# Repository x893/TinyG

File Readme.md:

Software from https://github.com/synthetos/TinyG

xboot-BT : change for Bluetooth module

xboot-loader : utility to upload (MS Visual Studio 2013) upload program with parameters -b 115200 -P COM14 -U flash:w:tinyg.hex

hardware : design files for http://akb77.com/g/cnc/tinyg-controller-for-cnc/

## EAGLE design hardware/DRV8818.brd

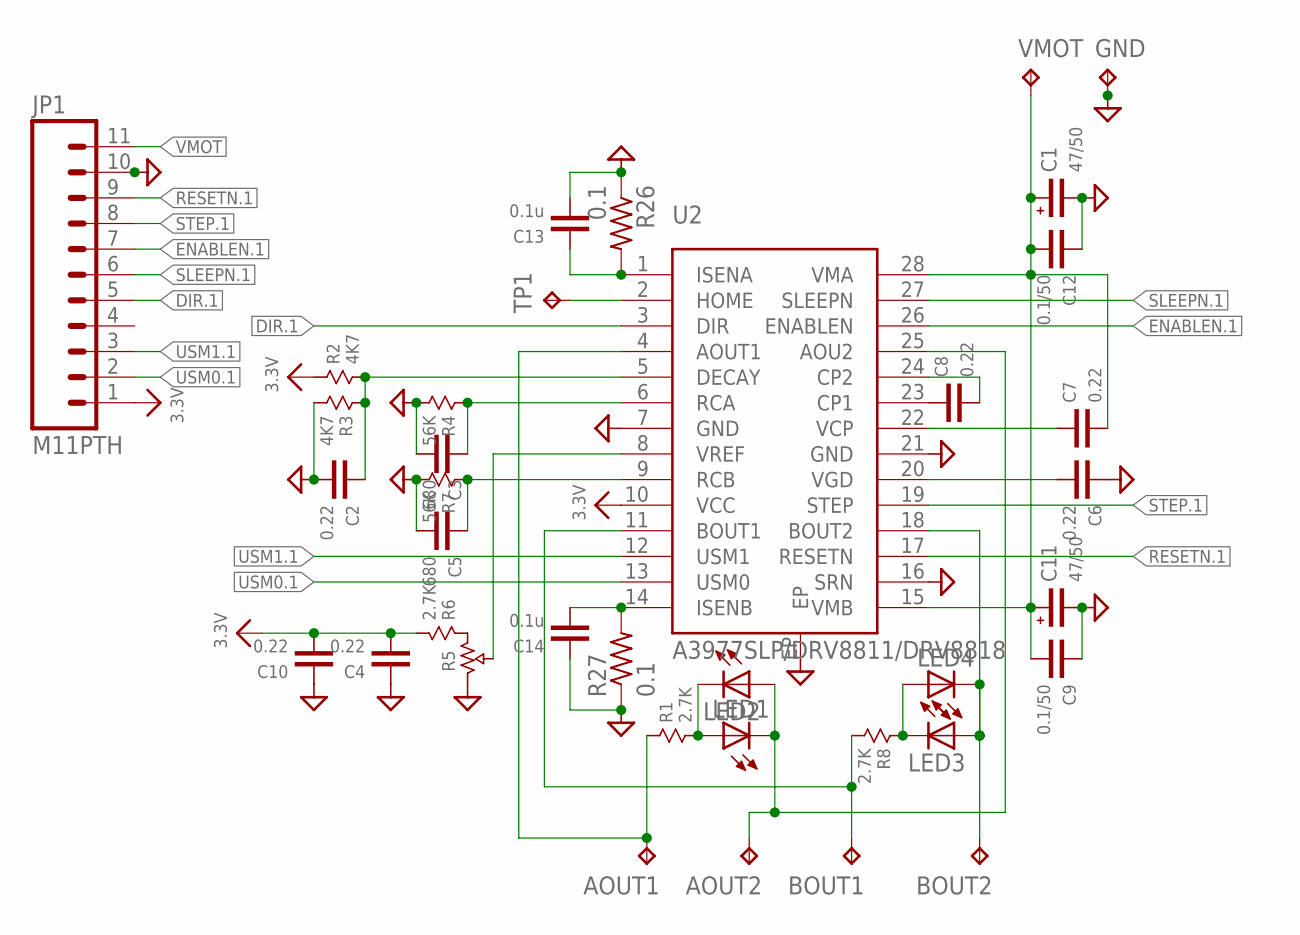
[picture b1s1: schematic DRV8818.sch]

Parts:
AOUT1, AOUT2: TPTP20R; TP20R
BOUT1, BOUT2: TPTP20R; TP20R
C1, C11: 47/50; CT7343
C2, C4, C6, C7, C8, C10: 0.22; 0603
C3, C5: 680; 0603
C9, C12: 0.1/50; 0603
C13, C14: 0.1u; 0603
GND: TPTP20R; TP20R
JP1: M11PTH; 1X11
LED1, LED2, LED3, LED4: LEDCHIP-LED0603; CHIP-LED0603
R1, R6, R8: 2.7K; 0603
R2, R3: 4K7; 0603
R4, R7: 56K; 0603
R5: PVZ3A
R26, R27: 0.1; R2512
TP1: TPTP08R; TP08R
U2: A3977SLP/DRV8811/DRV8818; SSOP28EP
VMOT: TPTP20R; TP20R

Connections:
3.3V: C4.1, C10.1, JP1.1, R2.1, R6.2, U2.10 (VCC)
AOUT1: AOUT1.TP, R1.1, U2.4 (AOUT1)
AOUT2: AOUT2.TP, LED1.C, LED2.A, U2.25 (AOU2)
BOUT1: BOUT1.TP, R8.2, U2.11 (BOUT1)
BOUT2: BOUT2.TP, LED3.A, LED4.C, U2.18 (BOUT2)
DIR.1: JP1.5, U2.3 (DIR)
ENABLEN.1: JP1.7, U2.26 (ENABLEN)
GND: C1.-, C2.1, C3.1, C4.2, C5.1, C6.2, C9.2, C10.2, C11.-, C12.2, C13.1, C14.2, GND.TP, JP1.10, R3.2, R4.2, R5.1, R7.2, R26.1, R27.1, U2.7 (GND), U2.16 (SRN), U2.21 (GND), U2.EP
unnamed: C14.1, R27.2, U2.14 (ISENB)
unnamed: LED3.C, LED4.A, R8.1
unnamed: LED1.A, LED2.C, R1.2
unnamed: C2.2, R2.2, R3.1, U2.5 (DECAY)
unnamed: C3.2, R4.1, U2.6 (RCA)
unnamed: R5.3, R6.1
unnamed: R5.2, U2.8 (VREF)
unnamed: C5.2, R7.1, U2.9 (RCB)
unnamed: C13.2, R26.2, U2.1 (ISENA)
unnamed: TP1.TP, U2.2 (HOME)
unnamed: C7.2, U2.22 (VCP)
unnamed: C6.1, U2.20 (VGD)
unnamed: C8.2, U2.23 (CP1)
unnamed: C8.1, U2.24 (CP2)
RESETN.1: JP1.9, U2.17 (RESETN)
SLEEPN.1: JP1.6, U2.27 (SLEEPN)
STEP.1: JP1.8, U2.19 (STEP)
USM0.1: JP1.2, U2.13 (USM0)
USM1.1: JP1.3, U2.12 (USM1)
VMOT: C1.+, C7.1, C9.1, C11.+, C12.1, JP1.11, U2.15 (VMB), U2.28 (VMA), VMOT.TP

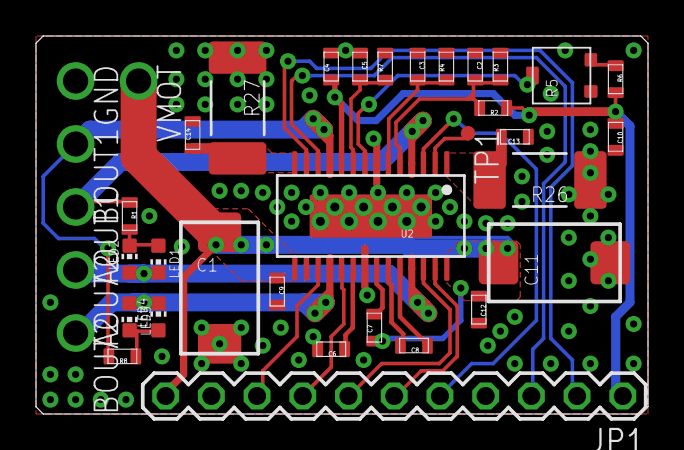
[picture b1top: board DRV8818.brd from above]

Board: 2 copper layers, 34.0 x 21.0 mm, 37 parts (0 on the bottom side), 28 nets.

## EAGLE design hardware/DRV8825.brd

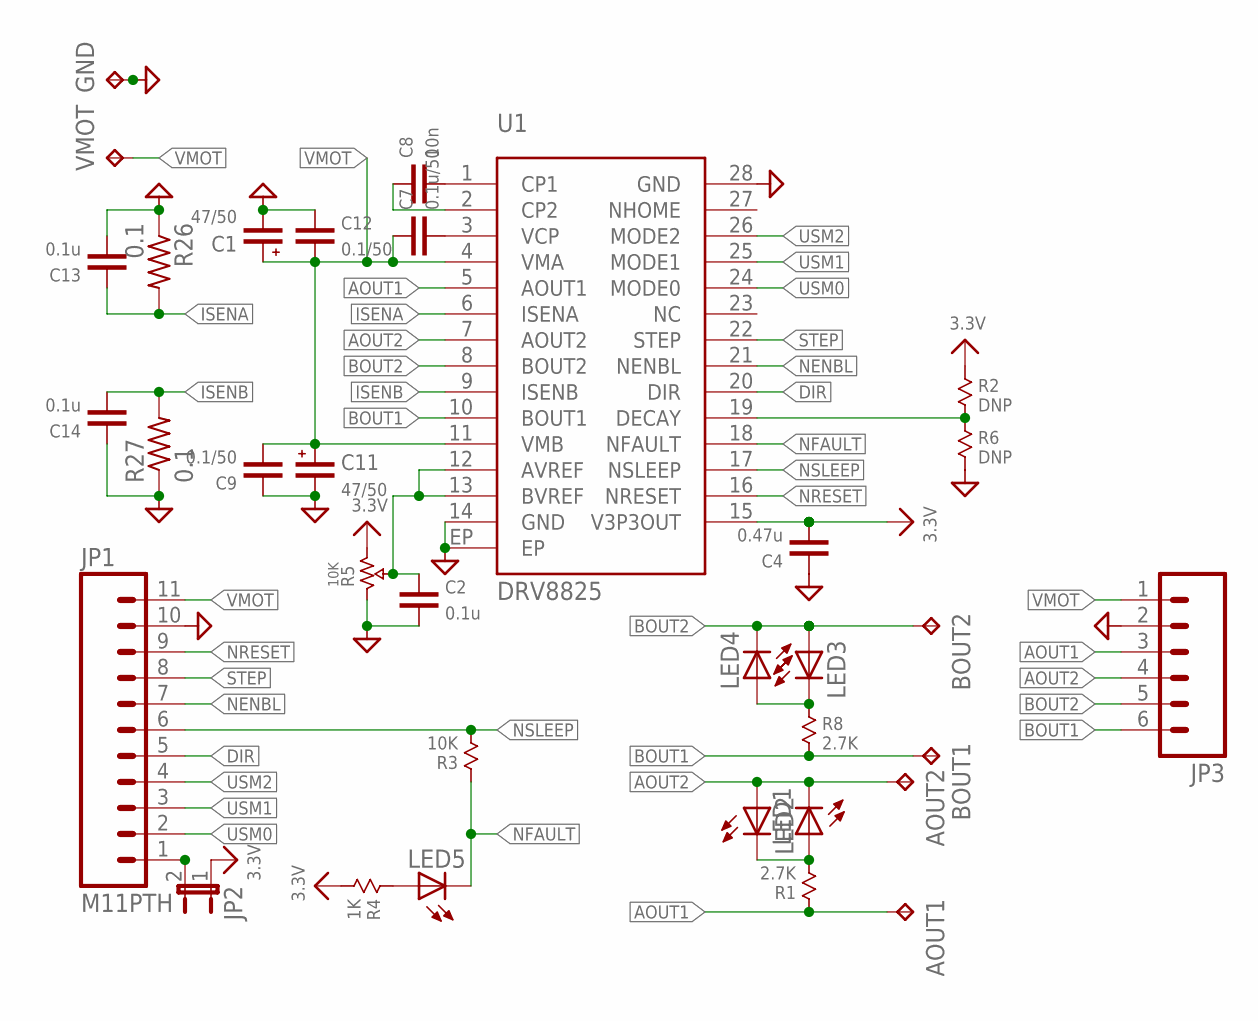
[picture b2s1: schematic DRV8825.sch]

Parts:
AOUT1, AOUT2: TPTP18R; TP18R
BOUT1, BOUT2: TPTP18R; TP18R
C1, C11: 47/50; CT7343
C2, C13, C14: 0.1u; 0603
C4: 0.47u; 0603
C7: 0.1u/50; 0603
C8: 10n; 0603
C9, C12: 0.1/50; 0603
GND: TPTP18R; TP18R
JP1: M11PTH; 1X11
JP2: JUMPER-2SMD-NO; SJ_2S-NO
JP3: M06SIP; 1X06
LED1, LED2, LED3, LED4, LED5: LEDCHIP-LED0603; CHIP-LED0603
R1, R8: 2.7K; 0603
R2, R6: DNP; 0603
R3: 10K; 0603
R4: 1K; 0603
R5: 10K; PVZ3A
R26, R27: 0.1; R2512
U1: DRV8825; SSOP28EP
VMOT: TPTP18R; TP18R

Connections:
3.3V: C4.1, JP2.1, R2.1, R4.2, R5.3, U1.15 (V3P3OUT)
AOUT1: AOUT1.TP, JP3.3, R1.1, U1.5 (AOUT1)
AOUT2: AOUT2.TP, JP3.4, LED1.C, LED2.A, U1.7 (AOUT2)
BOUT1: BOUT1.TP, JP3.6, R8.2, U1.10 (BOUT1)
BOUT2: BOUT2.TP, JP3.5, LED3.A, LED4.C, U1.8 (BOUT2)
DIR: JP1.5, U1.20 (DIR)
GND: C1.-, C2.1, C4.2, C9.2, C11.-, C12.2, C13.1, C14.2, GND.TP, JP1.10, JP3.2, R5.1, R6.2, R26.1, R27.1, U1.14 (GND), U1.28 (GND), U1.EP
ISENA: C13.2, R26.2, U1.6 (ISENA)
ISENB: C14.1, R27.2, U1.9 (ISENB)
unnamed: C8.1, U1.1 (CP1)
unnamed: LED3.C, LED4.A, R8.1
unnamed: LED1.A, LED2.C, R1.2
unnamed: C8.2, U1.2 (CP2)
unnamed: LED5.A, R4.1
unnamed: C7.1, U1.3 (VCP)
unnamed: C2.2, R5.2, U1.12 (AVREF), U1.13 (BVREF)
unnamed: R2.2, R6.1, U1.19 (DECAY)
unnamed: JP1.1, JP2.2
NENBL: JP1.7, U1.21 (NENBL)
NFAULT: LED5.C, R3.1, U1.18 (NFAULT)
NRESET: JP1.9, U1.16 (NRESET)
NSLEEP: JP1.6, R3.2, U1.17 (NSLEEP)
STEP: JP1.8, U1.22 (STEP)
USM0: JP1.2, U1.24 (MODE0)
USM1: JP1.3, U1.25 (MODE1)
USM2: JP1.4, U1.26 (MODE2)
VMOT: C1.+, C7.2, C9.1, C11.+, C12.1, JP1.11, JP3.1, U1.4 (VMA), U1.11 (VMB), VMOT.TP

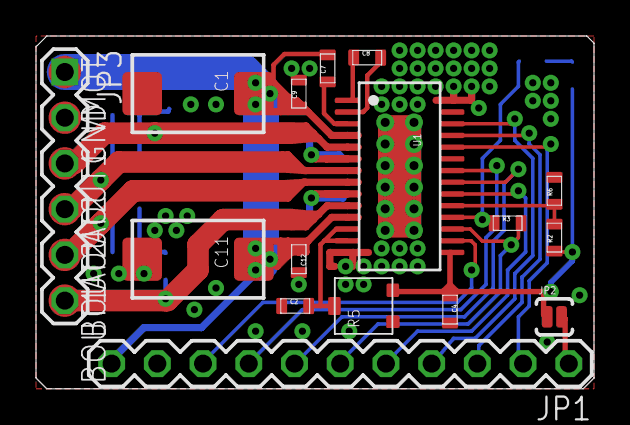
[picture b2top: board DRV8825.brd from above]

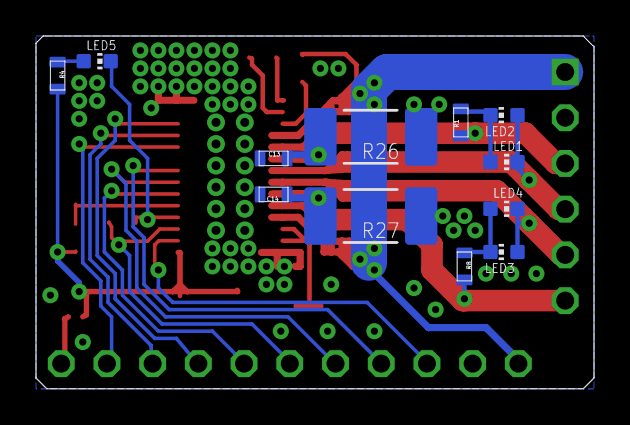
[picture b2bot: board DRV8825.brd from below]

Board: 2 copper layers, 31.0 x 19.6 mm, 34 parts (12 on the bottom side), 27 nets.

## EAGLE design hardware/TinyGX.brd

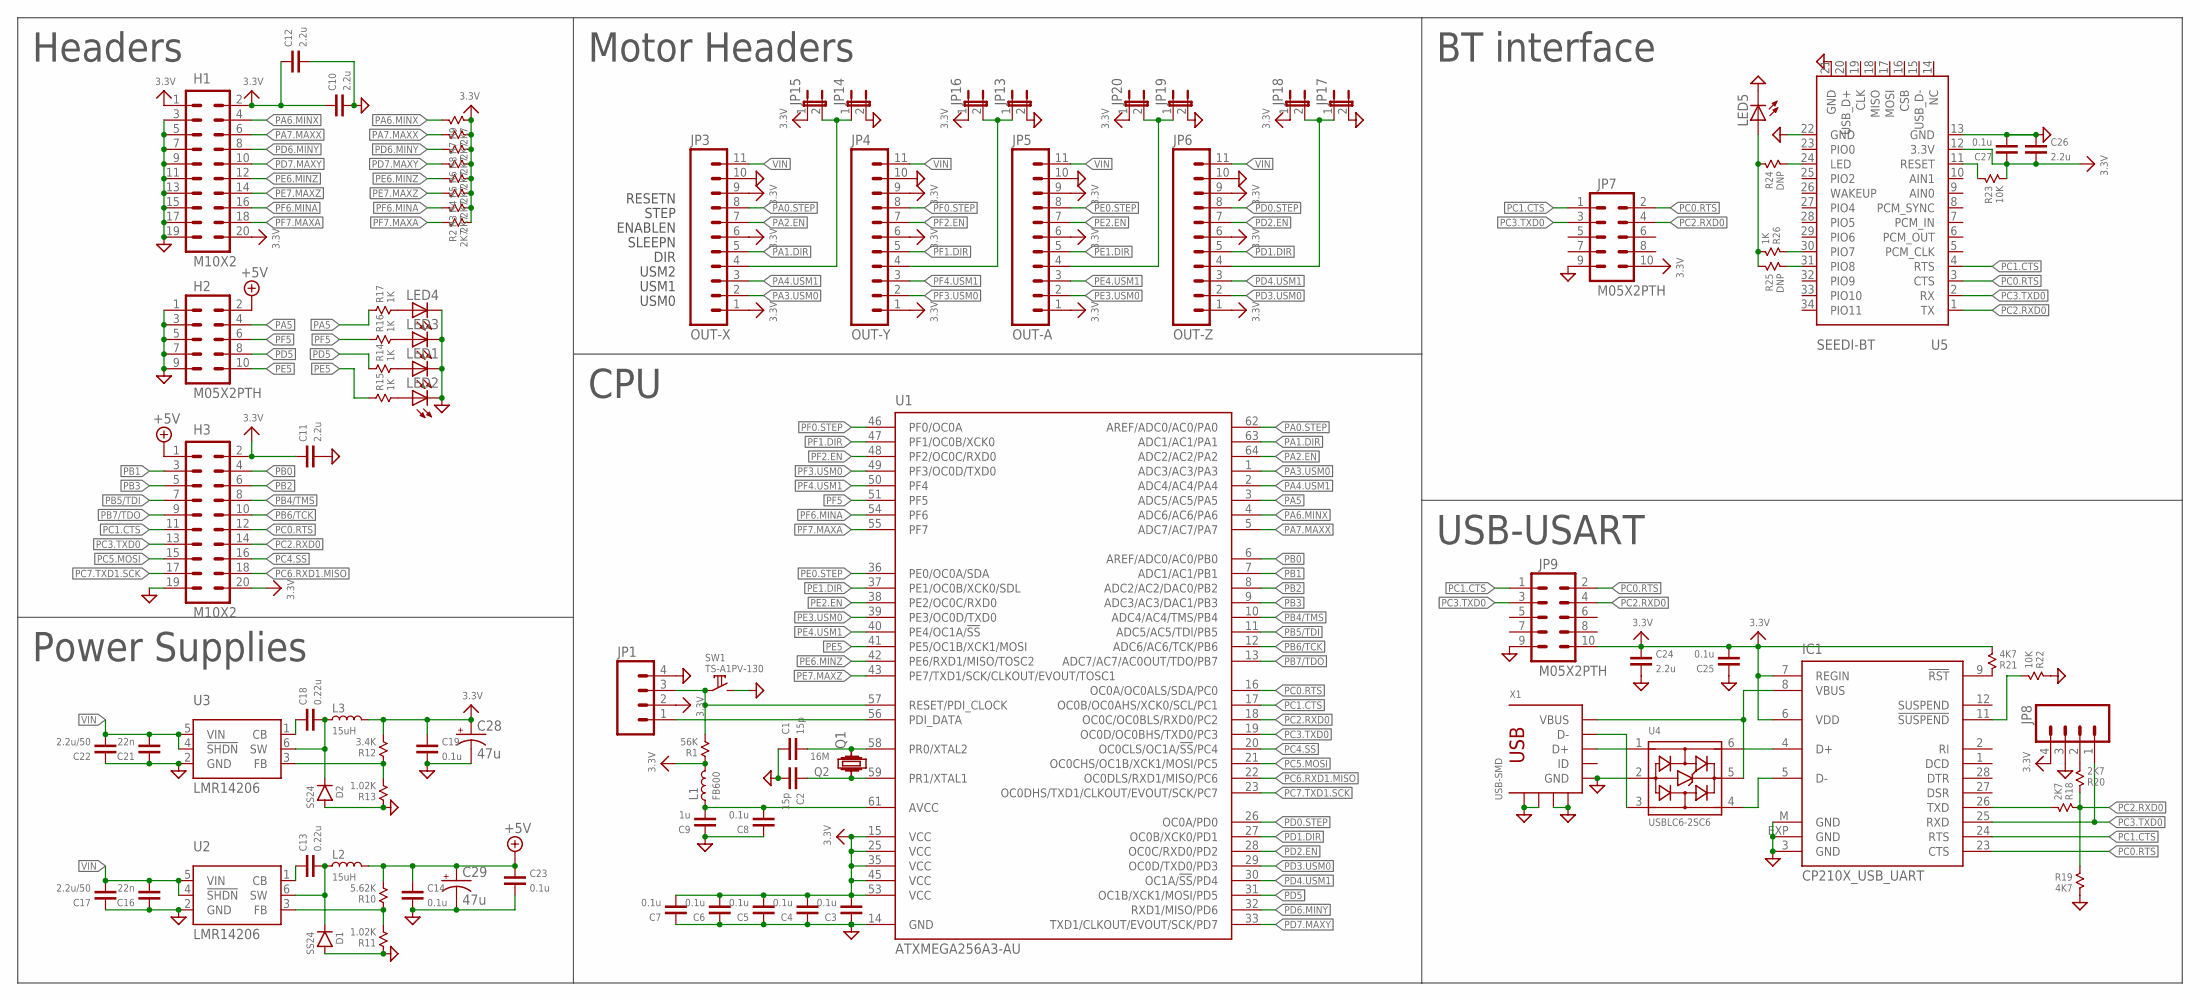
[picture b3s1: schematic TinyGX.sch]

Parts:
C1, C2: 15p; 0603
C3, C4, C5, C6, C7, C8, C14, C19, C23, C25, C27: 0.1u; 0603
C9: 1u; 0603
C10, C11, C12, C24, C26: 2.2u; 0603
C13, C18: 0.22u; 0603
C16, C21: 22n; 0603
C17, C22: 2.2u/50; 1206
C28, C29: 47u; CT3216
D1, D2: SS24; SMA
H1, H3: M10X2; 2X10
H2: M05X2PTH; AVR_ICSP
IC1: CP210X_USB_UART; MLP28
JP1, JP8: M04PTH; 1X04
JP3: OUT-X; 1X11
JP4: OUT-Y; 1X11
JP5: OUT-A; 1X11
JP6: OUT-Z; 1X11
JP7, JP9: M05X2PTH; AVR_ICSP
JP13, JP14, JP15, JP16, JP17, JP18, JP19, JP20: JUMPER-2SMD-NO; SJ_2S-NO
L1: FB600; 0603
L2, L3: 15uH; CDRH73
LED1, LED2, LED3, LED4, LED5: LEDCHIP-LED0603; CHIP-LED0603
Q1: CRYSTALHC49US; HC49US
Q2: 16M; KX-KT
R1: 56K; 0603
R2, R3, R4, R5, R6, R7, R8, R9, R18, R20: 2K7; 0603
R10: 5.62K; 0603
R11, R13: 1.02K; 0603
R12: 3.4K; 0603
R14, R15, R16, R17, R26: 1K; 0603
R19, R21: 4K7; 0603
R22, R23: 10K; 0603
R24, R25: DNP; 0603
SW1: TS-A1PV-130
U1: ATXMEGA256A3-AU; TQFP64-14X14
U2, U3: LMR14206; SOT23-6
U4: USBLC6-2SC6; SOT23-6
U5: SEEDI-BT
X1: USB-SMD; USB-MINIB

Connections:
3.3V: C3.1, C4.1, C5.1, C6.1, C7.1, C10.2, C11.2, C12.2, C19.2, C24.2, C25.1, C26.1, C27.2, C28.+, H1.1, H1.2, H1.20, H3.2, H3.20, IC1.6 (VDD), IC1.7 (REGIN), JP1.2, JP3.1, JP3.6, JP3.9, JP4.1, JP4.6, JP4.9, JP5.1, JP5.6, JP5.9, JP6.1, JP6.6, JP6.9, JP7.10, JP8.4, JP9.10, JP15.1, JP16.1, JP18.1, JP20.1, L1.2, L3.P$2 (2), R1.1, R2.2, R3.2, R4.2, R5.2, R6.2, R7.2, R8.2, R9.2, R12.2, R21.2, R23.2, U1.15 (VCC), U1.25 (VCC), U1.35 (VCC), U1.45 (VCC), U1.53 (VCC), U5.12 (3.3V)
+5V: C14.2, C23.2, C29.+, H2.2, H3.1, L2.P$2 (2), R10.2
GND: C1.2, C2.1, C3.2, C4.2, C5.2, C6.2, C7.2, C8.2, C9.2, C10.1, C11.1, C12.1, C14.1, C16.2, C17.2, C19.1, C21.2, C22.2, C23.1, C24.1, C25.2, C26.2, C27.1, C28.-, C29.-, D1.P$2 (A), D2.P$2 (A), H1.3, H1.5, H1.7, H1.9, H1.11, H1.13, H1.15, H1.17, H1.19, H2.1, H2.3, H2.5, H2.7, H2.9, H3.19, IC1.3 (GND), IC1.EXP (GND), IC1.M (GND), JP1.4, JP3.10, JP4.10, JP5.10, JP6.10, JP7.9, JP8.3, JP9.9, JP13.2, JP14.2, JP17.2, JP19.2, LED1.C, LED2.C, LED3.C, LED4.C, LED5.C, R11.1, R13.1, R19.2, R22.1, SW1.2, U1.14 (GND), U1.24 (GND), U1.34 (GND), U1.44 (GND), U1.52 (GND), U1.60 (GND), U2.2 (GND), U3.2 (GND), U4.2 (GND), U5.13 (GND), U5.21 (GND), U5.22 (GND), X1.GND, X1.GND@1 (GND), X1.GND@2 (GND), X1.GND@3 (GND), X1.GND@4 (GND)
unnamed: C1.1, Q1.2, Q2.2, U1.58 (PR0/XTAL2)
unnamed: C2.2, Q1.1, Q2.1, U1.59 (PR1/XTAL1)
unnamed: R10.1, R11.2, U2.3 (FB)
unnamed: LED1.A, R14.2
unnamed: C13.1, D1.P$1 (C), L2.P$1 (1), U2.6 (SW)
unnamed: R12.1, R13.2, U3.3 (FB)
unnamed: C13.2, U2.1 (CB)
unnamed: C8.1, C9.1, L1.1, U1.61 (AVCC)
unnamed: C18.1, D2.P$1 (C), L3.P$1 (1), U3.6 (SW)
unnamed: C18.2, U3.1 (CB)
unnamed: LED2.A, R15.2
unnamed: LED3.A, R16.2
unnamed: LED4.A, R17.2
unnamed: IC1.5 (D-), U4.4 (IO2)
unnamed: IC1.4 (D+), U4.6 (IO1)
unnamed: IC1.8 (VBUS), U4.5 (VBUS), X1.VBUS
unnamed: JP8.2, R20.2
unnamed: IC1.26 (TXD), R18.2
unnamed: IC1.9 (!RST), R21.1
unnamed: U4.3 (IO2), X1.D-
unnamed: U4.1 (IO1), X1.D+
unnamed: IC1.11 (!SUSPEND), R22.2
unnamed: JP3.4, JP14.1, JP15.2
unnamed: JP4.4, JP13.1, JP16.2
unnamed: JP5.4, JP19.1, JP20.2
unnamed: JP6.4, JP17.1, JP18.2
unnamed: R26.1, U5.30 (PIO7)
unnamed: R23.1, U5.11 (RESET)
unnamed: R24.2, U5.24 (LED)
unnamed: R25.2, U5.31 (PIO8)
unnamed: LED5.A, R24.1, R25.1, R26.2
PA0.STEP: JP3.8, U1.62 (AREF/ADC0/AC0/PA0)
PA1.DIR: JP3.5, U1.63 (ADC1/AC1/PA1)
PA2.EN: JP3.7, U1.64 (ADC2/AC2/PA2)
PA3.USM0: JP3.2, U1.1 (ADC3/AC3/PA3)
PA4.USM1: JP3.3, U1.2 (ADC4/AC4/PA4)
PA5: H2.4, R17.1, U1.3 (ADC5/AC5/PA5)
PA6.MINX: H1.4, R9.1, U1.4 (ADC6/AC6/PA6)
PA7.MAXX: H1.6, R7.1, U1.5 (ADC7/AC7/PA7)
PB0: H3.4, U1.6 (AREF/ADC0/AC0/PB0)
PB1: H3.3, U1.7 (ADC1/AC1/PB1)
PB2: H3.6, U1.8 (ADC2/AC2/DAC0/PB2)
PB3: H3.5, U1.9 (ADC3/AC3/DAC1/PB3)
PB4/TMS: H3.8, U1.10 (ADC4/AC4/TMS/PB4)
PB5/TDI: H3.7, U1.11 (ADC5/AC5/TDI/PB5)
PB6/TCK: H3.10, U1.12 (ADC6/AC6/TCK/PB6)
PB7/TDO: H3.9, U1.13 (ADC7/AC7/AC0OUT/TDO/PB7)
PC0.RTS: H3.12, IC1.23 (CTS), JP7.2, JP9.2, U1.16 (OC0A/OC0ALS/SDA/PC0), U5.3 (CTS)
PC1.CTS: H3.11, IC1.24 (RTS), JP7.1, JP9.1, U1.17 (OC0B/OC0AHS/XCK0/SCL/PC1), U5.4 (RTS)
PC2.RXD0: H3.14, JP7.4, JP9.4, R18.1, R19.1, R20.1, U1.18 (OC0C/OC0BLS/RXD0/PC2), U5.1 (TX)
PC3.TXD0: H3.13, IC1.25 (RXD), JP7.3, JP8.1, JP9.3, U1.19 (OC0D/OC0BHS/TXD0/PC3), U5.2 (RX)
PC4.SS: H3.16, U1.20 (OC0CLS/OC1A/!SS!/PC4)
PC5.MOSI: H3.15, U1.21 (OC0CHS/OC1B/XCK1/MOSI/PC5)
PC6.RXD1.MISO: H3.18, U1.22 (OC0DLS/RXD1/MISO/PC6)
PC7.TXD1.SCK: H3.17, U1.23 (OC0DHS/TXD1/CLKOUT/EVOUT/SCK/PC7)
PD0.STEP: JP6.8, U1.26 (OC0A/PD0)
PD1.DIR: JP6.5, U1.27 (OC0B/XCK0/PD1)
PD2.EN: JP6.7, U1.28 (OC0C/RXD0/PD2)
PD3.USM0: JP6.2, U1.29 (OC0D/TXD0/PD3)
PD4.USM1: JP6.3, U1.30 (OC1A/!SS!/PD4)
PD5: H2.8, R14.1, U1.31 (OC1B/XCK1/MOSI/PD5)
PD6.MINY: H1.8, R8.1, U1.32 (RXD1/MISO/PD6)
PD7.MAXY: H1.10, R6.1, U1.33 (TXD1/CLKOUT/EVOUT/SCK/PD7)
PDI: JP1.1, U1.56 (PDI_DATA)
PE0.STEP: JP5.8, U1.36 (PE0/OC0A/SDA)
PE1.DIR: JP5.5, U1.37 (PE1/OC0B/XCK0/SDL)
PE2.EN: JP5.7, U1.38 (PE2/OC0C/RXD0)
PE3.USM0: JP5.2, U1.39 (PE3/OC0D/TXD0)
PE4.USM1: JP5.3, U1.40 (PE4/OC1A/!SS)
PE5: H2.10, R15.1, U1.41 (PE5/OC1B/XCK1/MOSI)
PE6.MINZ: H1.12, R5.1, U1.42 (PE6/RXD1/MISO/TOSC2)
PE7.MAXZ: H1.14, R4.1, U1.43 (PE7/TXD1/SCK/CLKOUT/EVOUT/TOSC1)
PF0.STEP: JP4.8, U1.46 (PF0/OC0A)
PF1.DIR: JP4.5, U1.47 (PF1/OC0B/XCK0)
PF2.EN: JP4.7, U1.48 (PF2/OC0C/RXD0)
PF3.USM0: JP4.2, U1.49 (PF3/OC0D/TXD0)
PF4.USM1: JP4.3, U1.50 (PF4)
PF5: H2.6, R16.1, U1.51 (PF5)
PF6.MINA: H1.16, R3.1, U1.54 (PF6)
PF7.MAXA: H1.18, R2.1, U1.55 (PF7)
RST/PDC: JP1.3, R1.2, SW1.1, U1.57 (RESET/PDI_CLOCK)
VIN: C16.1, C17.1, C21.1, C22.1, JP3.11, JP4.11, JP5.11, JP6.11, U2.4 (!SHDN), U2.5 (VIN), U3.4 (!SHDN), U3.5 (VIN)

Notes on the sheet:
USM0
USM1
DIR
SLEEPN
ENABLEN
STEP
RESETN
USM2
BT interface
USB-USART
Motor Headers
CPU
Power Supplies
Headers

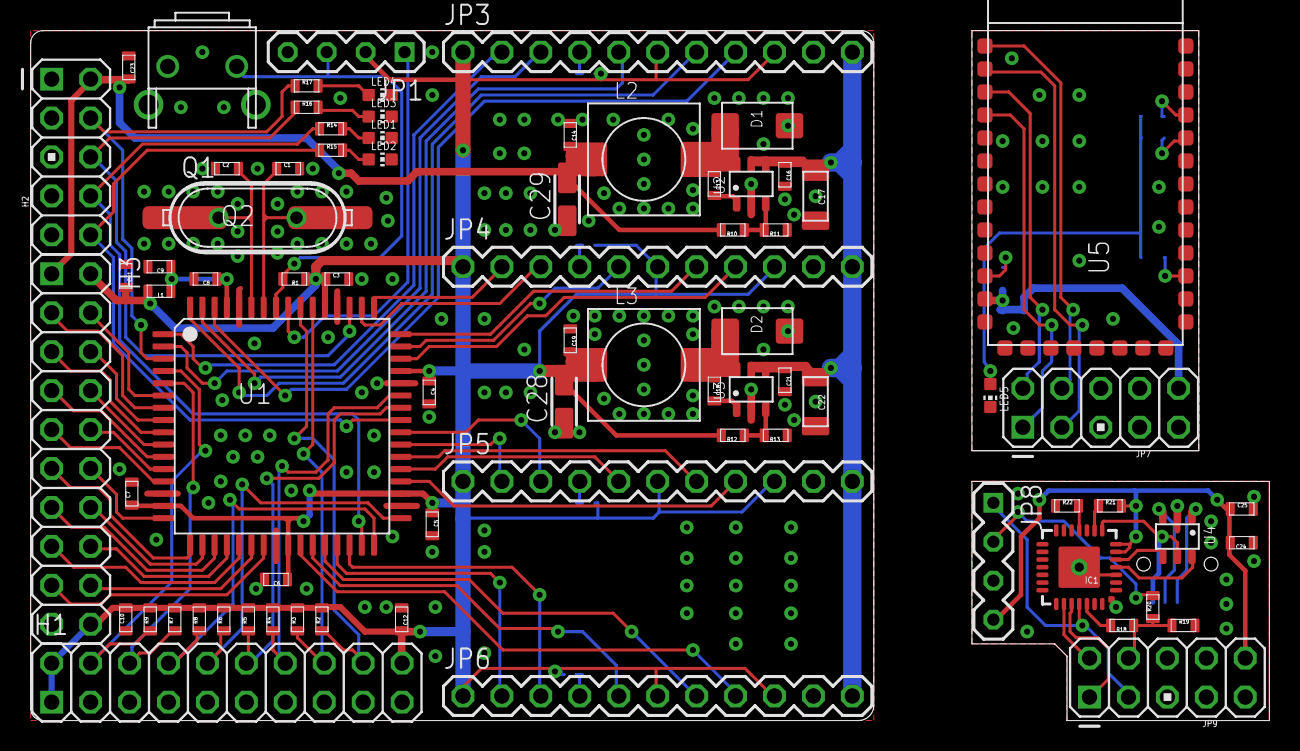
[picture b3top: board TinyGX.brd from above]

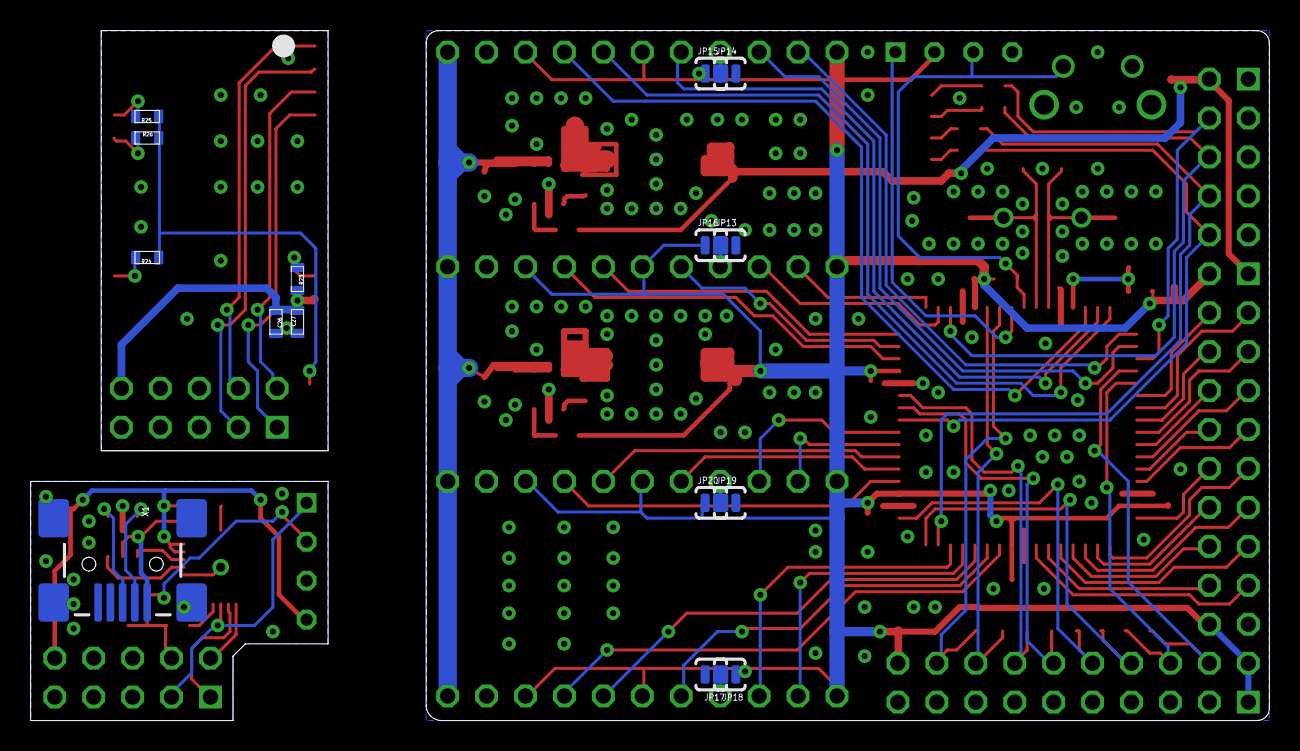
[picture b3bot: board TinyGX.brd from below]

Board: 2 copper layers, 80.8 x 45.0 mm, 92 parts (15 on the bottom side), 85 nets.

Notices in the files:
parts and their libraries:
microbuilder: This work is placed in the public domain, and may be freely used for commercial and non-commercial work with the following conditions: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
